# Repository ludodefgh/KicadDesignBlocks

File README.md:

# KicadDesignBlocks

Reusable KiCad circuit blocks: a schematic and its PCB layout, one self-contained
KiCad project per folder. Each project can be opened or shared on its own, for
example for an external review.

| Block | What it is | Status |
|---|---|---|
| [`TPS563208/`](TPS563208/) | Buck 5 V → 3.3 V / 1 A, TI TPS563208 (was TPS563201), 4 layers. Generated from the MultiSensors board (private repository) | layout done, not fabricated |
| [`TPS5430Buck/`](TPS5430Buck/) | Power input + buck based on the TI TPS5430: screw-terminal input, polyfuses (schematic note: "5/12/24V Power In") | earlier stand-alone project, history imported from the former `TPS5430Buck` repo |

## Conventions

- One folder per block, named after the main part, holding its own `.kicad_pro`.
- Symbols that are not in the standard KiCad libraries go in a project-local library
  (`sym/`, declared in the folder's `sym-lib-table`), so the project opens anywhere.
- `docs/` holds what a reviewer needs without KiCad: schematic PDF, layout image, and
  the sources the values came from.
- If a block is generated from another project, its README says so and names the
  script. Change it at the source and re-export.

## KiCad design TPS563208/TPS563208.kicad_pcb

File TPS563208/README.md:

# TPS563208 buck block: 5 V → 3.3 V / 1 A

A self-contained KiCad 10 project with just the TPS563208 and its passives, as laid
out in the MultiSensors sensor node (a private repository). It
exists so the power stage can be reviewed on its own, without the rest of the board.

The block started with the TPS563201 (folder `TPS563201/` until November 2026) and
switched to the TPS563208: same datasheet (SLVSD90), package, pinout and passives.
The schematic symbol is still named `TPS563201` for that reason.

| File | What it is |
|---|---|
| `TPS563208.kicad_pro` / `.kicad_sch` / `.kicad_pcb` | the project (open the `.kicad_pro`) |
| `docs/TPS563208-schematic.pdf` | schematic, readable without KiCad |
| `docs/TPS563208-layout.svg` | F.Cu, B.Cu, silkscreen and outline, readable without KiCad |
| `docs/webench/` | TI WEBENCH exports the part values came from (BOM CSV, layout images) |
| `sym/Block.kicad_sym` | project-local symbols, so the project opens on any machine |

## Operating point

| | Value |
|---|---|
| Input | 4.75–5.25 V, USB-C VBUS (the connector is outside this block) |
| Output | 3.32 V (0.768 V × (1 + 33.2 k / 10 k)) |
| Design current | 1 A (expected load: about 100 mA average, about 570 mA peak) |
| Switching frequency | 580 kHz (TPS563208, D-CAP2, forced continuous conduction (FCCM): no pulse skipping at light load) |
| Main loads on 3.3 V | MCU radio bursts, SCD41 CO₂ sensor (asks for a low-noise supply) |

## Parts

| Ref | Part | Value | LCSC |
|---|---|---|---|
| U11 | TI TPS563208DDCR, SOT-23-6 | | C468250 |
| L1 | Sunlord SWPA4030S3R3MT, 4 × 4 × 3 mm | 3.3 µH, Isat 3.6 A, DCR 52 mΩ | C15269 |
| C5, C6 | Samsung CL21A106KAYNNNE, 0805 | 10 µF 25 V X5R (input) | C15850 |
| C7 | 0805 | 100 nF (input, high-frequency) | |
| C8, C9 | Samsung CL21A226MAQNNNE, 0805 | 22 µF 25 V X5R (output) | C45783 |
| C4 | Yageo CC0603KRX7R9BB104, 0603 | 100 nF 50 V X7R (bootstrap) | C14663 |
| R5 | UNI-ROYAL 0603WAF3322T5E, 0603 | 33.2 k 1 % (feedback, upper) | C23003 |
| R6 | UNI-ROYAL 0603WAF1002T5E, 0603 | 10 k 1 % (feedback, lower) | C25804 |

- **L1**: at 4.75–5.25 V in, the ripple is 0.52–0.64 A peak-to-peak, so the inductor
  peaks at about 1.3 A at 1 A out.
- **Output capacitors**: two 22 µF give about 29.6 µF at 3.3 V DC bias (Samsung
  DC-bias curve), inside TI's 20–68 µF range. The Samsung part is marked NRND; its
  replacement CL21A226MAYNNN (C602037) gives about 27.4 µF.
- **C7**: optional in TI's Table 7-2, kept because the TPS563201EVM-715 fits it (C1)
  and WEBENCH reserves a spot for it.
- **U11, TPS563208 rather than TPS563201**: the TPS563201 runs in Eco-mode (pulse
  skipping) below about 0.29 A here, which gives a low-frequency ripple on 3.3 V.
  The SCD41 asks for at most 30 mV peak-to-peak on its unloaded supply (SCD4x
  datasheet, Table 4). The TPS563208 is the FCCM variant of the same datasheet
  (SLVSD90): it switches at a fixed frequency at any load, for about 3 mV of
  calculated ripple with the output capacitors here. The cost is a higher quiescent
  current and a lower light-load efficiency, which do not matter on USB power.
- **No 0402**: every passive is 0603 or larger, for hand assembly on a hot plate.
  R5 and R6 are pinned to 1 % parts, as TI asks for the divider (§7.2.2.2).

## Board and layout

- **4 layers: F.Cu / In1 = GND plane / In2 = +3.3 V plane / B.Cu.** The inner planes
  are cut to this block's outline. In the full board they cover the whole PCB.
- All parts are on the top side, for hot-plate assembly.
- The layout follows TI SLVSD90B §7.4 (fig. 7-18) and the TPS563201EVM-715 (SLVUAK7):
  - C7 sits across U11 pins 1 (GND) and 3 (VIN), at the same 1.9 mm pitch. The SW
    node leaves between its pads, under its body.
  - C5 and C6 sit right behind C7, on shared GND / +5 V copper areas.
  - L1 is above U11. The SW node is a small island: a copper area on F.Cu, plus a
    small area on B.Cu that crosses under the GND path through vias.
  - The input and output capacitors share one GND copper area that ties into U11
    pin 1.
  - The feedback divider sits on the quiet side of U11, away from L1 and SW.
- Design rules come from MultiSensors: 0.15 mm clearance, 0.4 mm minimum on power
  nets, and hand-assembly margins (0.5 mm between courtyards, with the pairs inside
  this block exempted because TI wants them tight) (`TPS563208.kicad_dru`).

## Where a review would help

1. **SW copper on B.Cu.** The SW pin reaches L1 through 6 vias and a 6.7 mm² area
   on B.Cu, as in TI's fig. 7-18; there is no direct path on F.Cu. It faces the
   +3.3 V plane at about 0.2 mm, which estimates to about 1 pF onto a heavily
   decoupled plane. A reviewer suggested keeping SW on the top layer instead; that
   needs a redraw of the block. Moving it onto In1 would cut the GND plane under the
   hot loop, so it is not an option; In2 (3.3 V plane) would be.
2. **Bootstrap path.** C4 stands upright to the right of L1, above U11 pin 6. VBST
   reaches it with a 0.6 mm trace, about 1 mm between the two pad edges. Its SW pad
   picks up SW from L1's SW pad on F.Cu: about 1.6 mm of trace between the two pad
   edges, over the GND plane.
3. **Feedback sense.** R5 measures the output through a via into the +3.3 V plane,
   not through a dedicated trace from the output capacitors (TI rule 6). R6 returns
   to GND through its own via, not a Kelvin connection to U11 pin 1 (rule 7).
4. **No series resistor on the bootstrap capacitor.** The TI EVM fits a 0 Ω (R5
   there) so the SW edges can be slowed for EMC. There is none here.

## Status

Not fabricated, not measured. The schematic passes ERC with 0 errors and 0 warnings.
The PCB passes DRC with 0 errors, 0 warnings, 0 unconnected items and 0
schematic/PCB mismatches.

## Source

This project is **generated** from MultiSensors with
`kicad/_generators/export_tps563208_block.py <this folder>`. The schematic is the U11
section of the MultiSensors schematic, copied as drawn (plus PWR_FLAGs on +5V and GND,
which live in the USB-C section there). The layout is the hand-drawn U11 group of the
MultiSensors board. Change the block in
MultiSensors and re-export; edits made only here are lost at the next export.

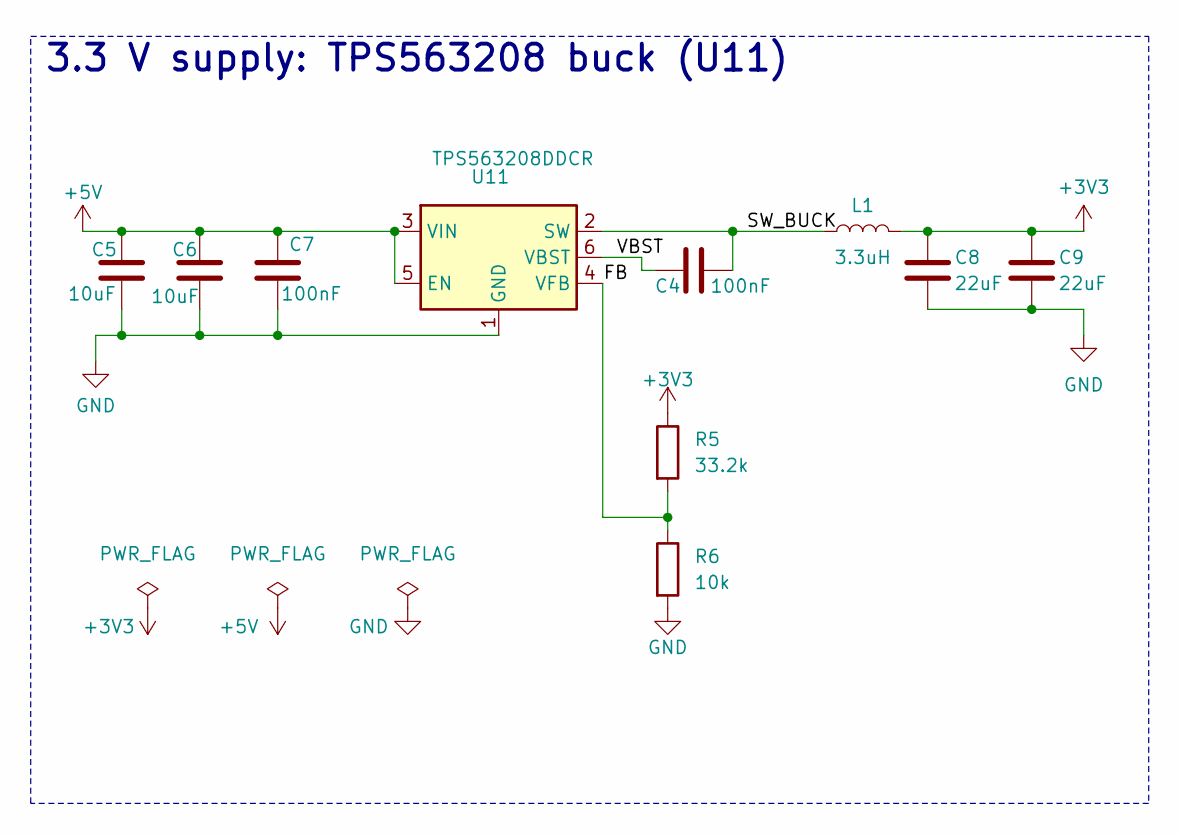
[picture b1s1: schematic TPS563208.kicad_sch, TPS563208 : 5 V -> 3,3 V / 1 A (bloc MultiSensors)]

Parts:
C4: 100nF; C_0603_1608Metric; MPN Yageo CC0603KRX7R9BB104 (100nF 50V X7R); LCSC C14663
C5, C6: 10uF; C_0805_2012Metric; MPN Samsung CL21A106KAYNNNE (10uF 25V X5R); LCSC C15850
C7: 100nF; C_0805_2012Metric; MPN Yageo CC0805KRX7R9BB104 (100nF 50V X7R); LCSC C49678
C8, C9: 22uF; C_0805_2012Metric; MPN Samsung CL21A226MAQNNNE (22uF 25V X5R); LCSC C45783
L1: 3.3uH; L_Sunlord_SWPA4030S; MPN Sunlord SWPA4030S3R3MT; LCSC C15269
R5: 33.2k; R_0603_1608Metric; MPN UNI-ROYAL 0603WAF3322T5E (33.2k 1%); LCSC C23003
R6: 10k; R_0603_1608Metric; MPN UNI-ROYAL 0603WAF1002T5E (10k 1%); LCSC C25804
U11: TPS563208DDCR; SOT-23-6; MPN TI TPS563208DDCR; LCSC C468250

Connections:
+3V3: C8.1, C9.1, L1.2, R5.1
+5V: C5.1, C6.1, C7.1, U11.3 (VIN), U11.5 (EN)
/FB: R5.2, R6.1, U11.4 (VFB)
/SW_BUCK: C4.2, L1.1, U11.2 (SW)
/VBST: C4.1, U11.6 (VBST)
GND: C5.2, C6.2, C7.2, C8.2, C9.2, R6.2, U11.1 (GND)

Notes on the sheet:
3.3 V supply: TPS563208 buck (U11)

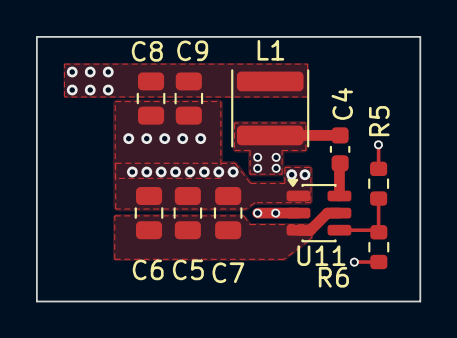
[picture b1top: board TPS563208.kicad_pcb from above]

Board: 4 copper layers, 21.3 x 14.7 mm, 10 parts (0 on the bottom side), 6 nets.

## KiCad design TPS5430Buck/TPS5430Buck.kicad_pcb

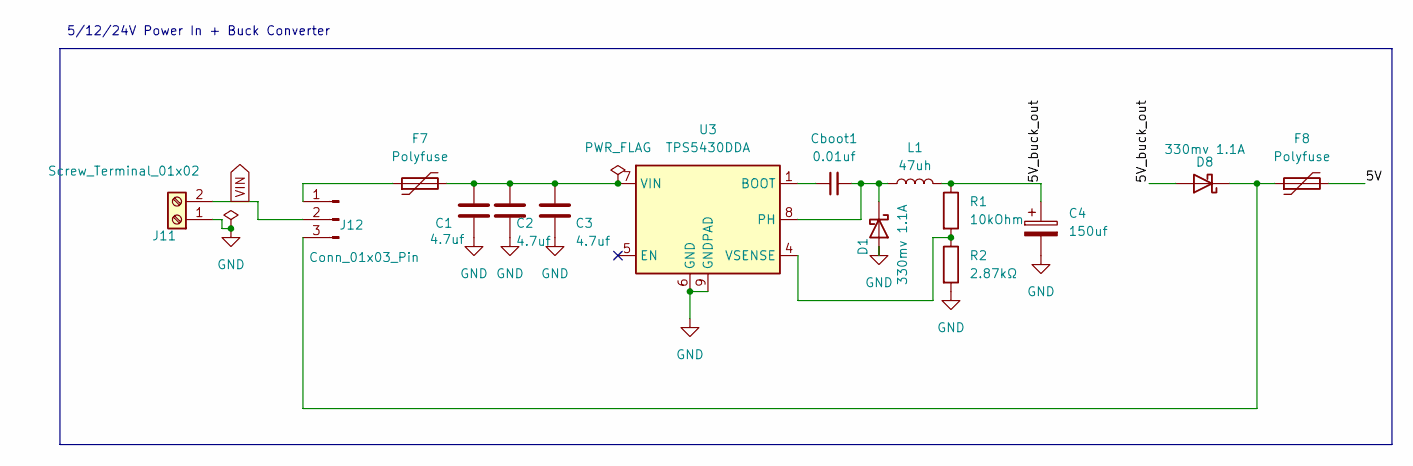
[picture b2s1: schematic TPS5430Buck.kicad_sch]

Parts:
C1, C2, C3: 4.7uf; C_1206_3216Metric; LCSC C29823
C4: 150uf; CP_EIA-7343-31_Kemet-D; LCSC C1953305
Cboot1: 0.01uf; R_0805_2012Metric; LCSC C1710
D1, D8: 330mv 1.1A; D_SMA; LCSC C8678
F7: Polyfuse; Fuse_1206_3216Metric; LCSC C7542958
F8: Polyfuse; Fuse_1206_3216Metric; LCSC C883127
J11: Screw_Terminal_01x02; TerminalBlock_Ningbo-Kagnex_HB9500M_1x02_P9.5mm; lcsc C601239
J12: Conn_01x03_Pin; PinHeader_1x03_P2.54mm_Vertical
L1: 47uh; L_7.3x7.3_H4.5; LCSC C168137
R1: 10kOhm; R_0201_0603Metric; LCSC C106225
R2: 2.87kΩ; R_0402_1005Metric; LCSC C334673
U3: TPS5430DDA; TI_SO-PowerPAD-8_ThermalVias; LCSC C9864

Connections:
/5V: F8.2
/5V_buck_out: C4.1, D8.2 (A), L1.2, R1.1
GND: C1.2, C2.2, C3.2, C4.2, D1.2 (A), J11.1, R2.2, U3.6 (GND), U3.9 (GNDPAD)
unnamed: Cboot1.2, D1.1 (K), L1.1, U3.8 (PH)
unnamed: D8.1 (K), F8.1, J12.3
unnamed: F7.1, J12.1
unnamed: Cboot1.1, U3.1 (BOOT)
unnamed: C1.1, C2.1, C3.1, F7.2, U3.7 (VIN)
unnamed: R1.2, R2.1, U3.4 (VSENSE)
VIN: J11.2, J12.2

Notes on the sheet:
5/12/24V Power In + Buck Converter

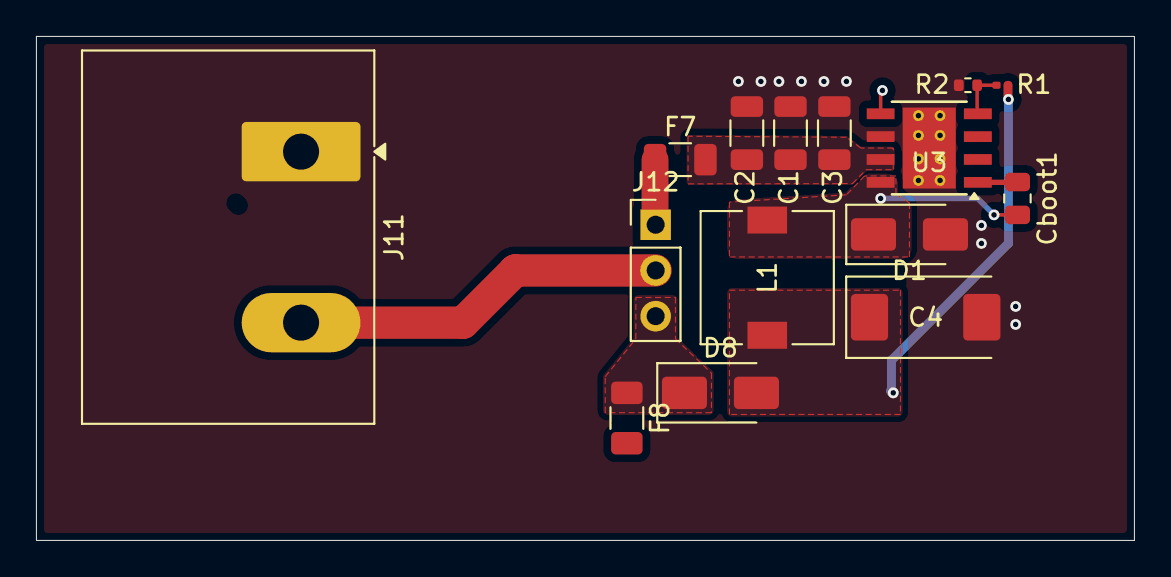
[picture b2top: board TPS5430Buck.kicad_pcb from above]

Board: 2 copper layers, 61.0 x 28.0 mm, 15 parts (0 on the bottom side), 9 nets.
